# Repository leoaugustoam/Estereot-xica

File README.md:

# Estereot-xica
Projeto voltado ao controle da maquina esteriotaxica - VOID3D

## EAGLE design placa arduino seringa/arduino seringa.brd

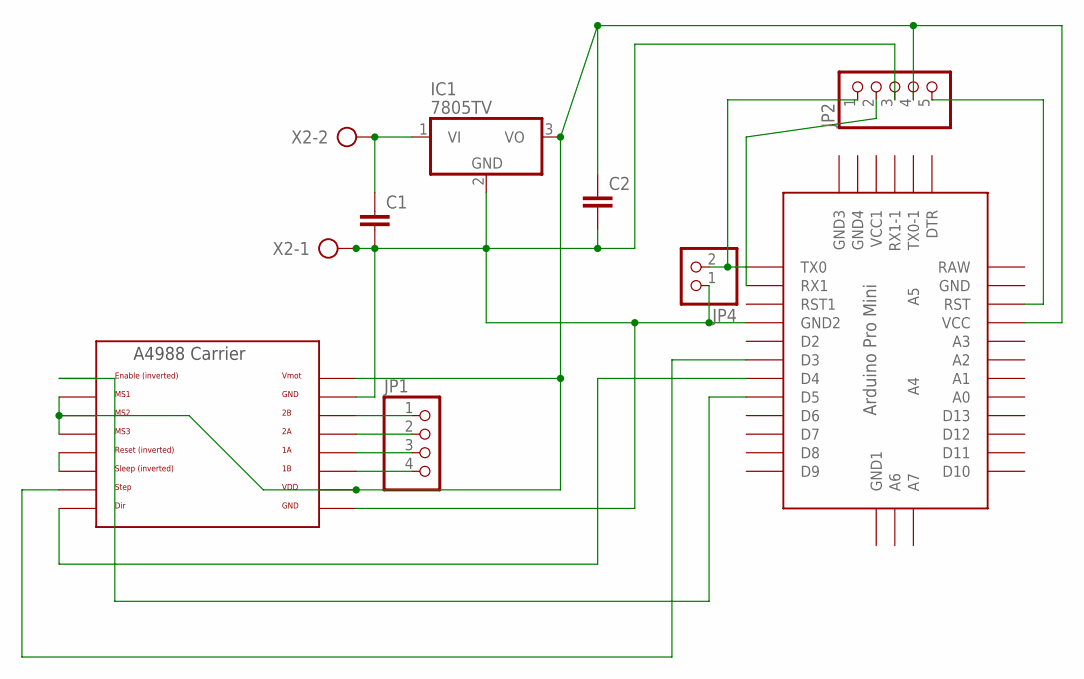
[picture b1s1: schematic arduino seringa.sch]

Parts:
C1, C2: C5/3; C5B3
IC1: 7805TV; TO220V
JP1: PINHD-1X4; 1X04
JP2: PINHD-1X5; 1X05
JP4: PINHD-1X2; 1X02
U$1: ABK-PRO-MINI
U$2: A4988BREAKOUT
X2: AK500/2

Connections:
unnamed: JP2.1, JP4.2, U$1.TX0
unnamed: C1.2, C2.2, IC1.2 (GND), JP2.3, JP4.1, U$1.GND1 (GND2), U$2.GND, U$2.GND@0 (GND), X2.1
unnamed: C1.1, IC1.1 (VI), X2.2
unnamed: JP2.5, U$1.RST
unnamed: JP2.2, U$1.RX1
unnamed: JP1.1, U$2.2B
unnamed: JP1.2, U$2.2A
unnamed: JP1.3, U$2.1A
unnamed: JP1.4, U$2.1B
unnamed: U$1.D5, U$2.EN
unnamed: C2.1, IC1.3 (VO), JP2.4, U$1.VCC, U$2.MS1, U$2.MS2, U$2.MS3, U$2.VDD, U$2.VMOT
unnamed: U$2.RST, U$2.SLP (SLEEP)
unnamed: U$1.D3, U$2.STEP
unnamed: U$1.D4, U$2.DIR

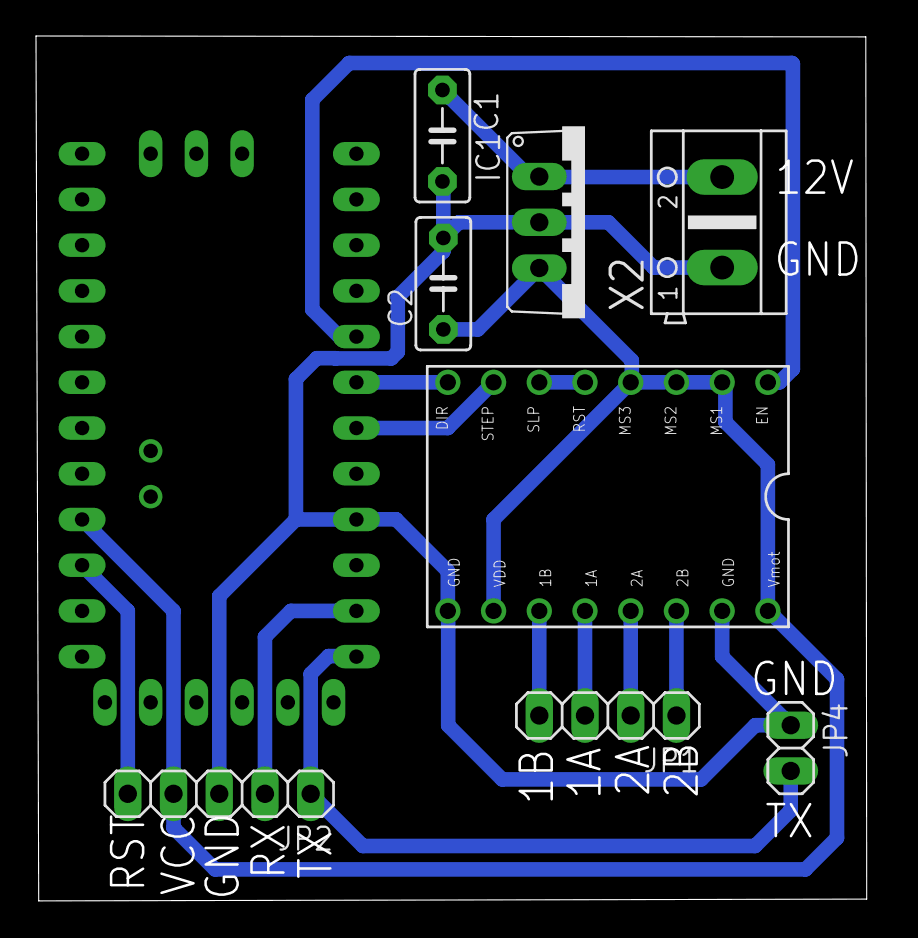
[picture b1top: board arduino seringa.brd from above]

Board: 2 copper layers, 46.2 x 48.0 mm, 9 parts (0 on the bottom side), 14 nets.

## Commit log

2017-10-23 add pastas restantes
    add pastas restantes
2017-10-23 reparo offset
2018-02-15 Versão 2018
    15 de Fev
    -Melhorias na camera
    -Versão final com todas as funcionalidades
2018-02-15 v2018
2018-02-15 Revert "Add files via upload"
    This reverts commit b9d67426b2fc42344040d20d2c6accf463bb729f.
2018-05-02 Versão finalizada com compensação na seringa
2020-11-17 ajuste versão qt
